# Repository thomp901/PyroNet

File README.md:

# PyroNet
Early Fire Detection: Purdue Senior Design Project

Team Members:
Sebastian Carrizosa
Kameron Jackson
Diego Ramirez
Garrison Thompson

## Download Specific Folders

To download **only** the a specific folder (e.g. hardware/, csp/) that contains the relevant files, run the following commands:

```bash
git clone --filter=blob:none --no-checkout https://github.com/thomp901/PyroNet.git
cd PyroNet
git sparse-checkout init --cone
git sparse-checkout set FOLDER/
git checkout main
```

Replace `FOLDER` with the specfic folder.

Then, you can `pull`, `add`, `commit`, and `push` like normal.

## Pushing

To push, go to the project directory in your terminal and enter the following commands:

```bash
git add .
git commit -m 'YOUR MESSAGE'
git push
```

Replace `YOUR MESSAGE` with a brief description of your changes.

## Discarding your changes

To **discard your changes** and pull the latest version, enter: 

```bash
git fetch --all
git reset --hard origin/main
```

> [!WARNING]
> Warning: This will permanently delete any local work.

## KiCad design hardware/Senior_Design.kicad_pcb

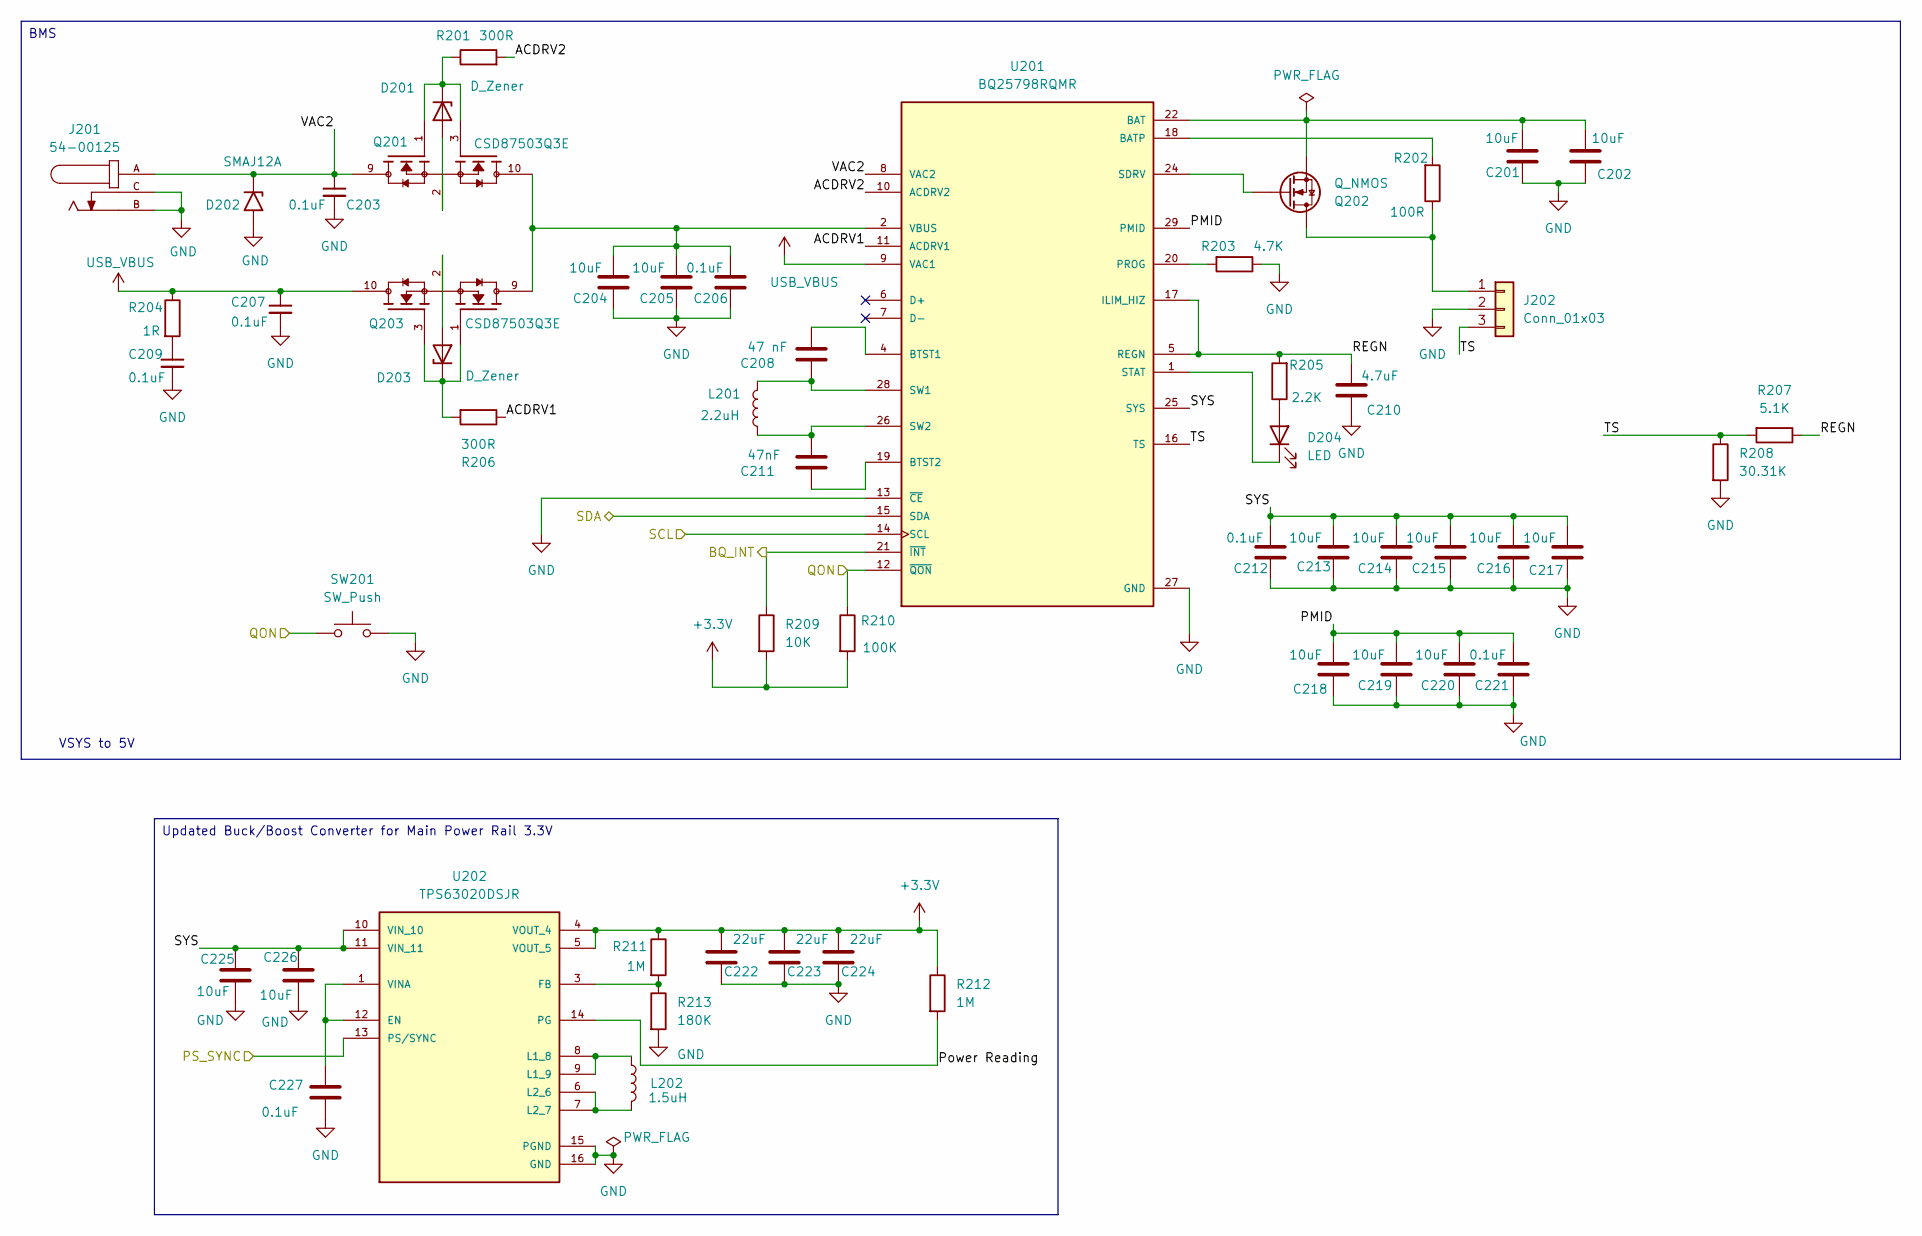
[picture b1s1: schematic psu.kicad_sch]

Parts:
C201, C202, C225, C226: 10uF; C_0603_1608Metric
C203, C207, C209: 0.1uF; C_0805_2012Metric
C204, C205, C213, C214, C215, C216, C217, C218, C219, C220: 10uF; C_0805_2012Metric
C206, C212, C221: 0.1uF; C_0402_1005Metric
C208: 47 nF; C_0603_1608Metric
C210: 4.7uF; C_0603_1608Metric
C211: 47nF; C_0603_1608Metric
C222, C223, C224: 22uF; C_0603_1608Metric
C227: 0.1uF; C_0603_1608Metric
D201, D203: D_Zener; D_SOD-123
D202: SMAJ12A; D_SMA
D204: LED; LED_0805_2012Metric
J201: 54-00125; TENSILITY_54-00125; PARTREV A; DigiKey_Part_Number 839-54-00125-ND
J202: Conn_01x03; JST_PH_S3B-PH-K_1x03_P2.00mm_Horizontal
L201: 2.2uH; L_Bourns_SRP7028A_7.3x6.6mm
L202: 1.5uH; L_Wuerth_MAPI-4020
Q201, Q203: CSD87503Q3E; TRANS_CSD87503Q3ET; PARTREV SEPTEMBER 2017; DigiKey_Part_Number 296-47497-1-ND
Q202: Q_NMOS; SOT-23_Handsoldering
R201, R206: 300R; R_0805_2012Metric
R202: 100R; R_0805_2012Metric
R203: 4.7K; R_0805_2012Metric
R204: 1R; R_0805_2012Metric
R205: 2.2K; R_0805_2012Metric
R207: 5.1K; R_0805_2012Metric
R208: 30.31K; R_0805_2012Metric
R209: 10K; R_0805_2012Metric
R210: 100K; R_0805_2012Metric
R211: 1M; R_0603_1608Metric
R212: 1M; R_0805_2012Metric
R213: 180K; R_0603_1608Metric
SW201: SW_Push; SW_SPST_TL3305A
U201: BQ25798RQMR; IC_BQ25798RQMR; PARTREV B
U202: TPS63020DSJR; IC_TPS63020DSJR

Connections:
+3.3V: C222.2, C223.2, C224.2, R209.2, R210.2, R211.1, R212.1, U202.4 (VOUT_4), U202.5 (VOUT_5); also elsewhere on the board
/BME 688 and SPS30/SCL: U201.14 (SCL); also elsewhere on the board
/BME 688 and SPS30/SDA: U201.15 (SDA); also elsewhere on the board
/BMS/ACDRV1: R206.1, U201.11 (ACDRV1)
/BMS/ACDRV2: R201.2, U201.10 (ACDRV2)
/BMS/BQ_INT: R209.1, U201.21 (~INT); also elsewhere on the board
/BMS/PMID: C218.1, C219.1, C220.1, C221.1, U201.29 (PMID)
/BMS/PS_SYNC: U202.13 (PS/SYNC); also elsewhere on the board
/BMS/Power Reading: R212.2, U202.14 (PG)
/BMS/QON: R210.1, SW201.1, U201.12 (~QON); also elsewhere on the board
/BMS/REGN: C210.1, R205.2, R207.1, U201.5 (REGN), U201.17 (ILIM_HIZ)
/BMS/SYS: C212.1, C213.1, C214.1, C215.1, C216.1, C217.1, C225.1, C226.1, U201.25 (SYS), U202.10 (VIN_10), U202.11 (VIN_11)
/BMS/TS: J202.3, R207.2, R208.1, U201.16 (TS)
/BMS/VAC2: C203.1, D202.1 (A1), J201.A, Q201.9, Q201.9.1, Q201.9.2, U201.8 (VAC2)
BAT: C201.1, C202.1, Q202.2 (S), U201.22 (BAT), U201.23 (BAT)
GND: C201.2, C202.2, C203.2, C204.2, C205.2, C206.2, C207.2, C209.2, C210.2, C212.2, C213.2, C214.2, C215.2, C216.2, C217.2, C218.2, C219.2, C220.2, C221.2, C222.1, C223.1, C224.1, C225.2, C226.2, C227.2, D202.2 (A2), J201.B, J201.C, J202.2, R203.1, R208.2, R213.2, SW201.2, U201.13 (~CE), U201.27 (GND), U202.2 (GND), U202.15 (PGND), U202.16 (GND), U202.17 (GND), U202.18 (GND), U202.19 (GND), U202.20 (GND), U202.21 (GND), U202.22 (GND), U202.23 (GND), U202.24 (GND), U202.25 (GND), U202.26 (GND), U202.27 (GND), U202.28 (GND), U202.29 (GND), U202.30 (GND); also elsewhere on the board
unnamed: C204.1, C205.1, C206.1, Q201.10, Q201.10.1, Q201.10.2, Q203.9, Q203.9.1, Q203.9.2, U201.2 (VBUS), U201.3 (VBUS)
unnamed: C209.1, R204.2
unnamed: D201.2 (A), Q201.2, Q201.4
unnamed: D201.1 (K), Q201.1, Q201.3, R201.1
unnamed: D203.2 (A), Q203.2, Q203.4
unnamed: D203.1 (K), Q203.1, Q203.3, R206.2
unnamed: D204.2 (A), R205.1
unnamed: D204.1 (K), U201.1 (STAT)
unnamed: J202.1, Q202.1 (D), R202.1
unnamed: Q202.3 (G), U201.24 (SDRV)
unnamed: R202.2, U201.18 (BATP)
unnamed: C208.1, U201.4 (BTST1)
unnamed: C211.2, U201.19 (BTST2)
unnamed: R203.2, U201.20 (PROG)
unnamed: C208.2, L201.2, U201.28 (SW1)
unnamed: C211.1, L201.1, U201.26 (SW2)
unnamed: C227.1, U202.1 (VINA), U202.12 (EN)
unnamed: R211.2, R213.1, U202.3 (FB)
unnamed: L202.1, U202.8 (L1_8), U202.9 (L1_9)
unnamed: L202.2, U202.6 (L2_6), U202.7 (L2_7)
USB_VBUS: C207.1, Q203.10, Q203.10.1, Q203.10.2, R204.1, U201.9 (VAC1); also elsewhere on the board

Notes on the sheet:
VSYS to 5V
Updated Buck/Boost Converter for Main Power Rail 3.3V
BMS

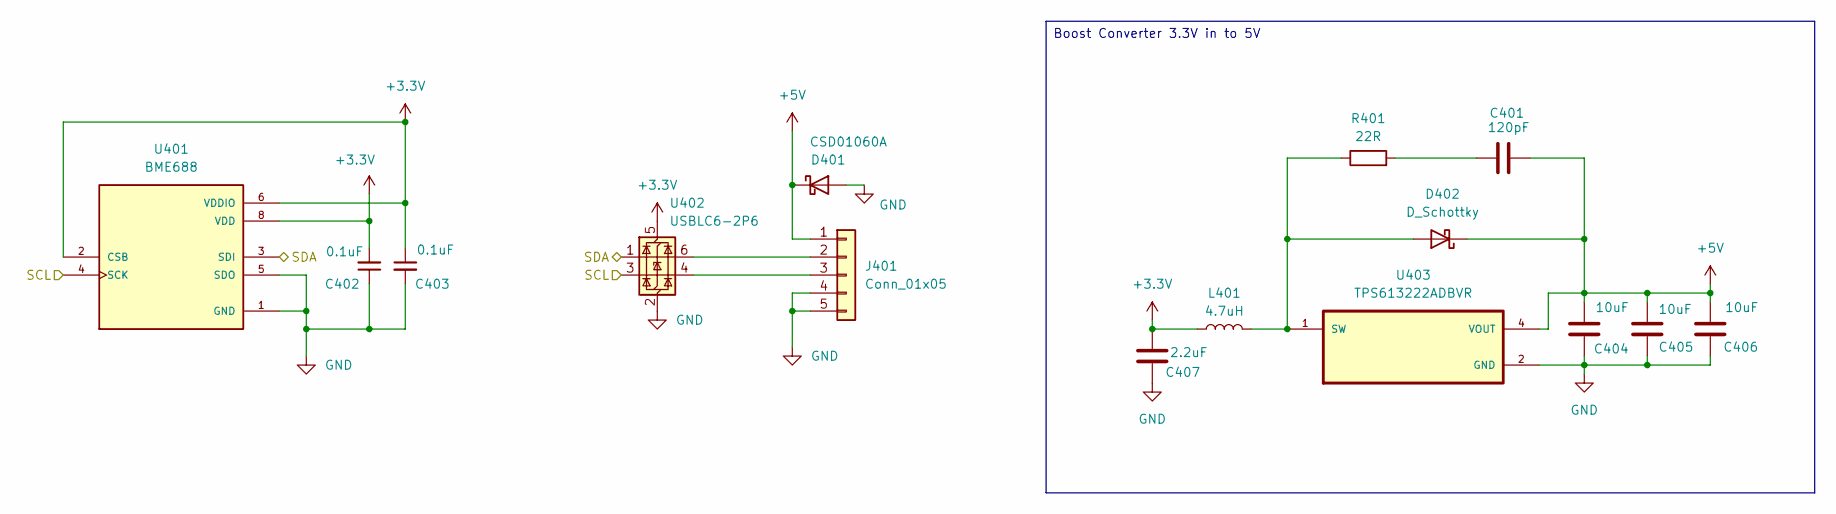
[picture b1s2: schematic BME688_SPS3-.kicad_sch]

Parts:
C401: 120pF; C_0402_1005Metric
C402, C403: 0.1uF; C_0805_2012Metric
C404, C405, C406: 10uF; C_0603_1608Metric
C407: 2.2uF; C_0603_1608Metric
D401: CSD01060A; D_SOD-123
D402: D_Schottky; D_0805_2012Metric
J401: Conn_01x05; JST_ZH_B5B-ZR_1x05_P1.50mm_Vertical
L401: 4.7uH; L_1008_2520Metric
R401: 22R; R_0402_1005Metric
U401: BME688; IC_BME688; PARTREV 1.0
U402: USBLC6-2P6; SOT-666
U403: TPS613222ADBVR; SOT95P280X145-5N; DigiKey_Part_Number 296-50503-1-ND

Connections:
+3.3V: C402.2, C403.1, C407.2, L401.1, U401.2 (CSB), U401.6 (VDDIO), U401.8 (VDD), U402.5 (VBUS); also elsewhere on the board
+5V: C401.1, C404.2, C405.2, C406.2, D401.1 (K), D402.1 (K), J401.1, U403.4 (VOUT)
/BME 688 and SPS30/SCL: U401.4 (SCK), U402.3 (I/O2); also elsewhere on the board
/BME 688 and SPS30/SDA: U401.3 (SDI), U402.1 (I/O1); also elsewhere on the board
GND: C402.1, C403.2, C404.1, C405.1, C406.1, C407.1, D401.2 (A), J401.4, J401.5, U401.1 (GND), U401.5 (SDO), U401.7 (GND), U402.2 (GND), U403.2 (GND); also elsewhere on the board
unnamed: C401.2, R401.2
unnamed: D402.2 (A), L401.2, R401.1, U403.1 (SW)
unnamed: J401.2, U402.6 (I/O1)
unnamed: J401.3, U402.4 (I/O2)

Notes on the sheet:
Boost Converter 3.3V in to 5V

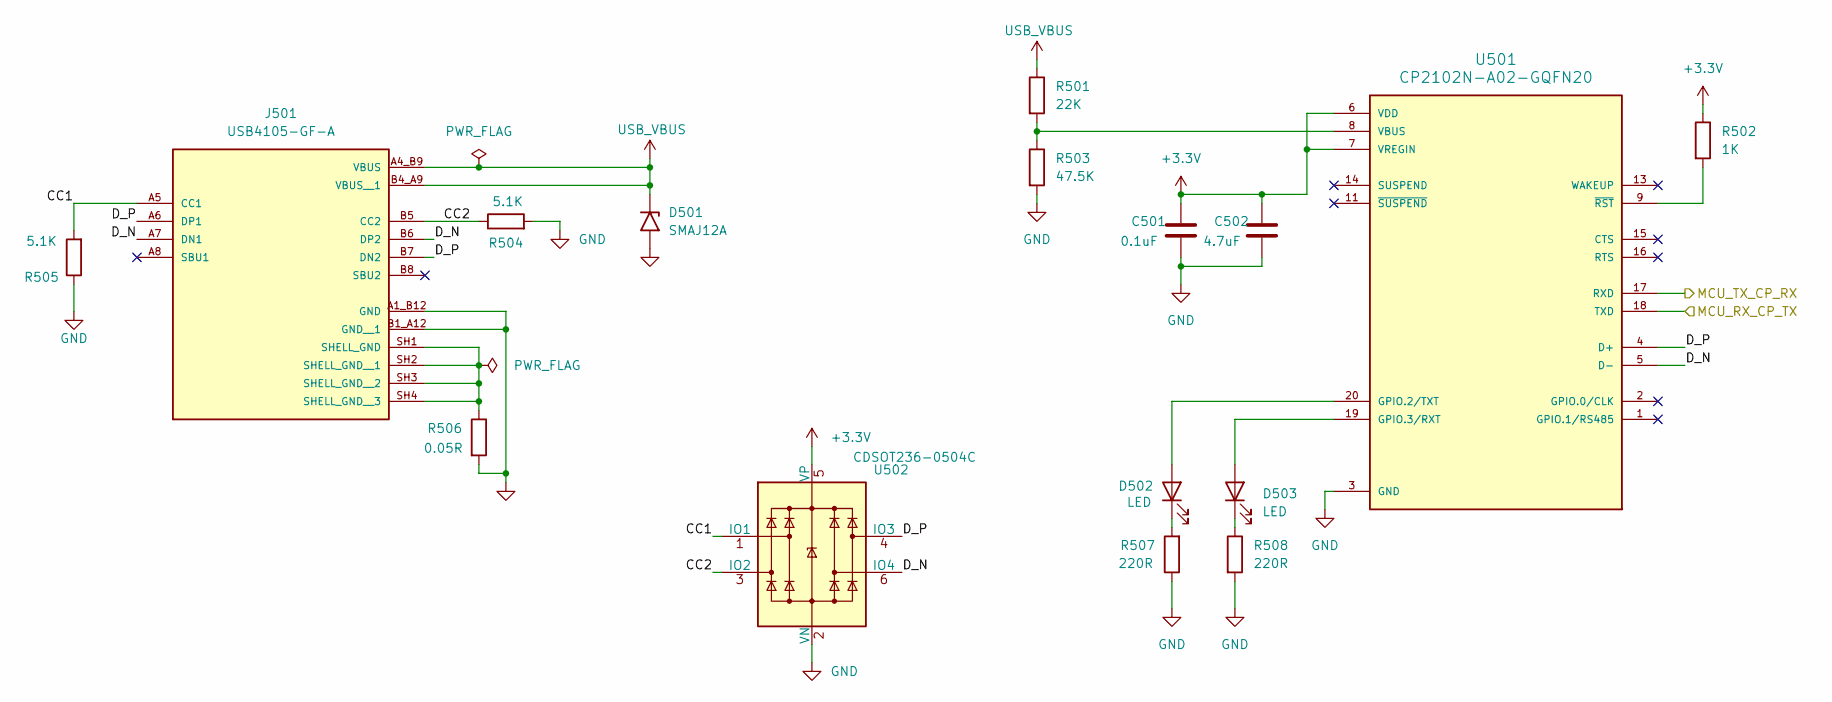
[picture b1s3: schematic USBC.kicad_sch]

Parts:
C501: 0.1uF; C_0603_1608Metric
C502: 4.7uF; C_0603_1608Metric
D501: SMAJ12A; D_SMA
D502, D503: LED; LED_0805_2012Metric
J501: USB4105-GF-A; GCT_USB4105-GF-A; PARTREV B4
R501: 22K; R_0805_2012Metric
R502: 1K; R_0805_2012Metric
R503: 47.5K; R_0805_2012Metric
R504, R505: 5.1K; R_0805_2012Metric
R506: 0.05R; R_0805_2012Metric
R507, R508: 220R; R_0805_2012Metric
U501: CP2102N-A02-GQFN20; SILABS_CP2102N-A02-GQFN20R; PARTREV 1.3
U502: CDSOT236-0504C; SOT-23-6

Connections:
+3.3V: C501.1, C502.1, R502.1, U501.6 (VDD), U501.7 (VREGIN), U502.5 (VP); also elsewhere on the board
/MCU/MCU_RX_CP_TX: U501.18 (TXD); also elsewhere on the board
/MCU/MCU_TX_CP_RX: U501.17 (RXD); also elsewhere on the board
/USB-C/CC1: J501.A5 (CC1), R505.2, U502.1 (IO1)
/USB-C/CC2: J501.B5 (CC2), R504.1, U502.3 (IO2)
/USB-C/D_N: J501.A7 (DN1), J501.B6 (DP2), U501.5 (D-), U502.6 (IO4)
/USB-C/D_P: J501.A6 (DP1), J501.B7 (DN2), U501.4 (D+), U502.4 (IO3)
GND: C501.2, C502.2, D501.2 (A2), J501.A1_B12 (GND), J501.B1_A12 (GND__1), R503.2, R504.2, R505.1, R506.2, R507.1, R508.2, U501.3 (GND), U501.12 (GND), U501.21 (GND), U502.2 (VN); also elsewhere on the board
unnamed: D502.2 (A), U501.20 (GPIO.2/TXT)
unnamed: D502.1 (K), R507.2
unnamed: D503.2 (A), U501.19 (GPIO.3/RXT)
unnamed: D503.1 (K), R508.1
unnamed: J501.SH1 (SHELL_GND), J501.SH2 (SHELL_GND__1), J501.SH3 (SHELL_GND__2), J501.SH4 (SHELL_GND__3), R506.1
unnamed: R501.2, R503.1, U501.8 (VBUS)
unnamed: R502.2, U501.9 (~RST)
USB_VBUS: D501.1 (A1), J501.A4_B9 (VBUS), J501.B4_A9 (VBUS__1), R501.1; also elsewhere on the board

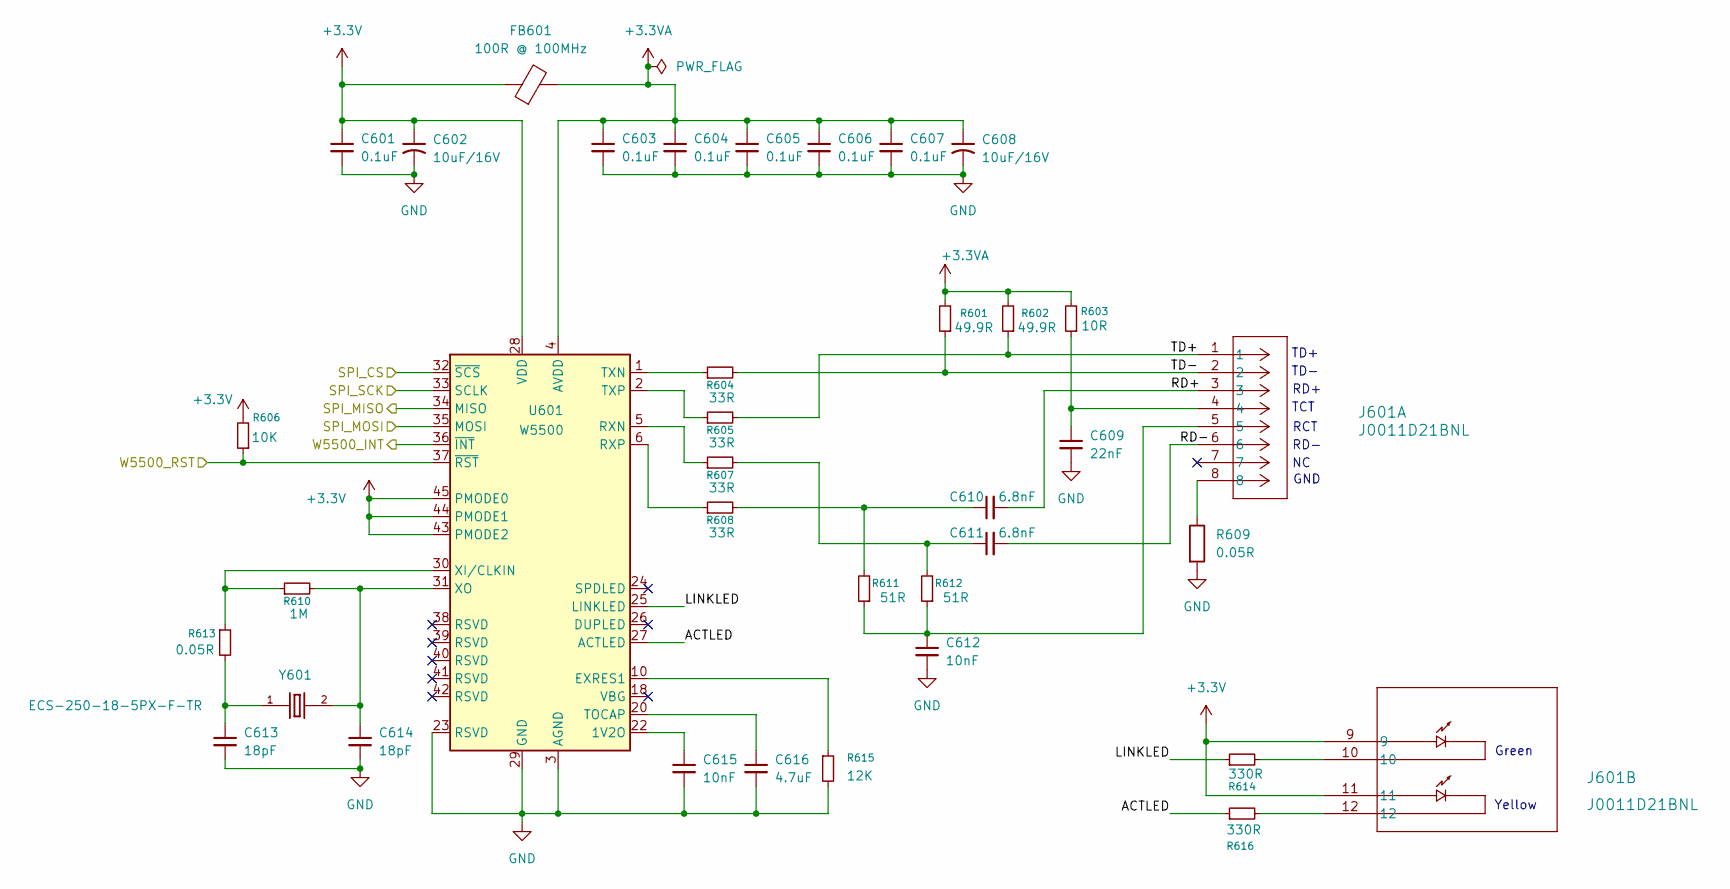
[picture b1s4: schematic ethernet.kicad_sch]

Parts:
C601, C603, C604, C605, C606, C607: 0.1uF; C_0603_1608Metric
C602, C608: 10uF/16V; C_0603_1608Metric
C609: 22nF; C_0805_2012Metric
C610, C611: 6.8nF; C_0805_2012Metric
C612, C615: 10nF; C_0805_2012Metric
C613, C614: 18pF; C_0805_2012Metric
C616: 4.7uF; C_0805_2012Metric
FB601: 100R @ 100MHz; R_0603_1608Metric
J601: J0011D21BNL; CONN_J0011D21B_PUL
R601, R602: 49.9R; R_0805_2012Metric
R603: 10R; R_0805_2012Metric
R604, R605, R607, R608: 33R; R_0805_2012Metric
R606: 10K; R_0603_1608Metric
R609, R613: 0.05R; R_0805_2012Metric
R610: 1M; R_0805_2012Metric
R611, R612: 51R; R_0805_2012Metric
R614, R616: 330R; R_0805_2012Metric
R615: 12K; R_0805_2012Metric
U601: W5500; LQFP-48_7x7mm_P0.5mm
Y601: ECS-250-18-5PX-F-TR; XTAL_ECS-250-18-5PX-F-TR; PARTREV 2017; DigiKey_Part_Number XC1305CT-ND

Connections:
+3.3V: C601.1, C602.1, FB601.1, J601.9, J601.11, R606.2, U601.28 (VDD), U601.43 (PMODE2), U601.44 (PMODE1), U601.45 (PMODE0); also elsewhere on the board
+3.3VA: C603.1, C604.1, C605.1, C606.1, C607.1, C608.1, FB601.2, R601.2, R602.2, R603.2, U601.4 (AVDD), U601.8 (AVDD), U601.11 (AVDD), U601.15 (AVDD), U601.17 (AVDD), U601.21 (AVDD)
/Ethernet/ACTLED: R616.1, U601.27 (ACTLED)
/Ethernet/LINKLED: R614.1, U601.25 (LINKLED)
/Ethernet/RD+: C610.2, J601.3
/Ethernet/RD-: C611.2, J601.6
/Ethernet/SPI_CS: U601.32 (~SCS); also elsewhere on the board
/Ethernet/SPI_MISO: U601.34 (MISO); also elsewhere on the board
/Ethernet/SPI_MOSI: U601.35 (MOSI); also elsewhere on the board
/Ethernet/SPI_SCK: U601.33 (SCLK); also elsewhere on the board
/Ethernet/TD+: J601.1, R602.1, R605.2
/Ethernet/TD-: J601.2, R601.1, R604.2
/Ethernet/W5500_INT: U601.36 (~INT); also elsewhere on the board
/Ethernet/W5500_RST: R606.1, U601.37 (~RST); also elsewhere on the board
GND: C601.2, C602.2, C603.2, C604.2, C605.2, C606.2, C607.2, C608.2, C609.2, C612.2, C613.2, C614.2, C615.2, C616.2, R609.2, R615.2, U601.3 (AGND), U601.9 (AGND), U601.14 (AGND), U601.16 (AGND), U601.19 (AGND), U601.23 (RSVD), U601.29 (GND), U601.48 (AGND); also elsewhere on the board
unnamed: C609.1, J601.4, R603.1
unnamed: C610.1, R608.2, R611.2
unnamed: C611.1, R607.2, R612.2
unnamed: C612.1, J601.5, R611.1, R612.1
unnamed: C613.1, R613.2, Y601.1
unnamed: J601.8, R609.1
unnamed: J601.10, R614.2
unnamed: J601.12, R616.2
unnamed: C615.1, U601.22 (1V2O)
unnamed: R615.1, U601.10 (EXRES1)
unnamed: R607.1, U601.5 (RXN)
unnamed: R608.1, U601.6 (RXP)
unnamed: C616.1, U601.20 (TOCAP)
unnamed: R604.1, U601.1 (TXN)
unnamed: R605.1, U601.2 (TXP)
unnamed: R610.1, R613.1, U601.30 (XI/CLKIN)
unnamed: C614.1, R610.2, U601.31 (XO), Y601.2

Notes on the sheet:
TD+
GND
TD-
TCT
Green
RCT
Yellow
RD+
RD-

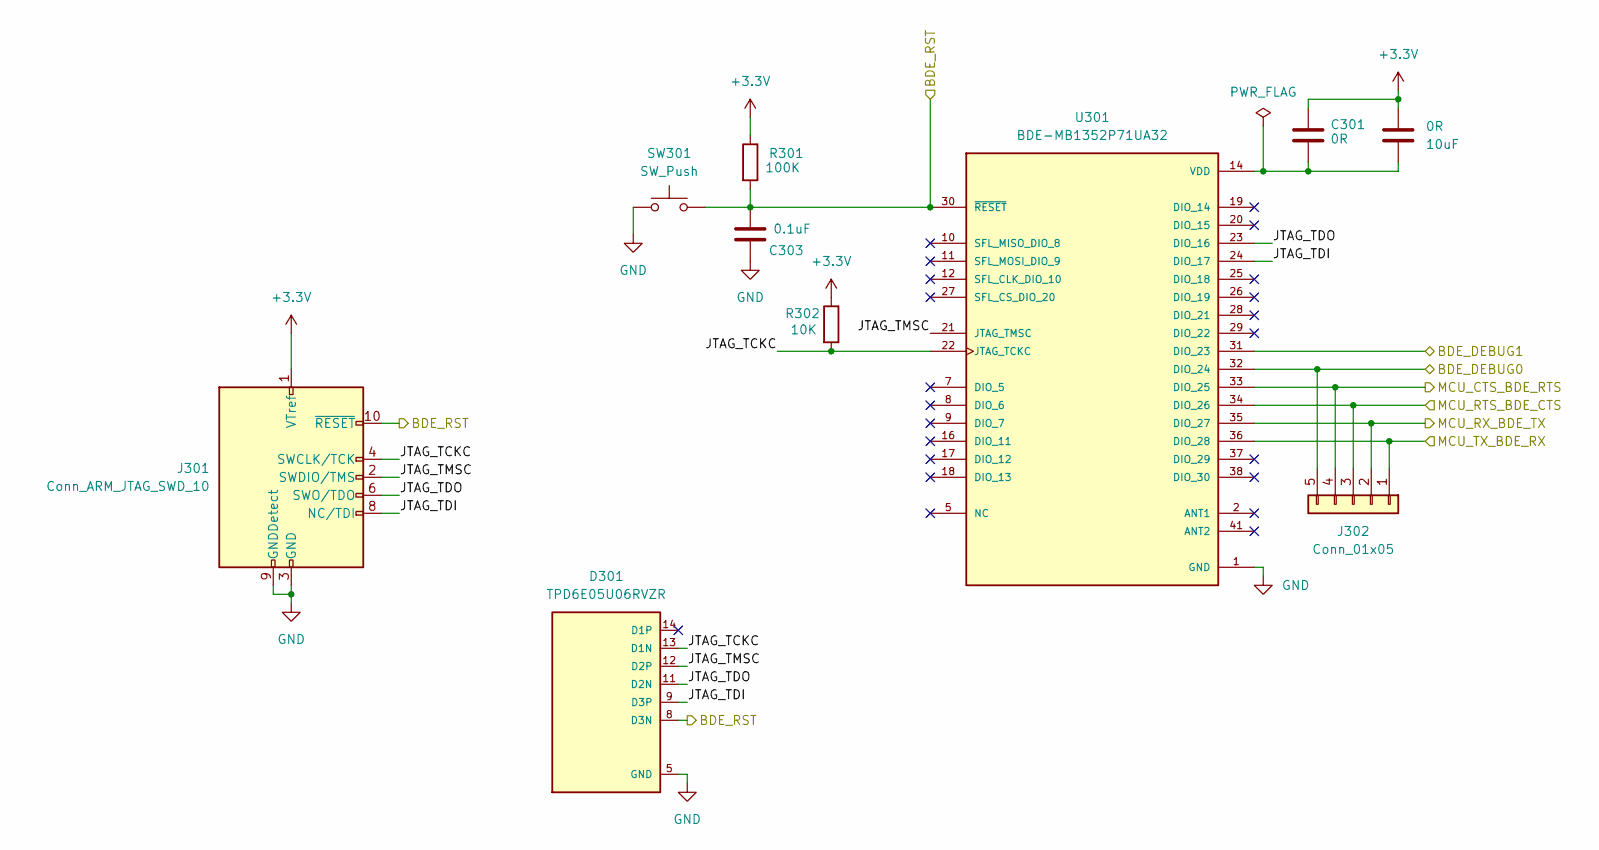
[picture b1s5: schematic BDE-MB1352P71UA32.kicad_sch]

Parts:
0R: 10uF; C_0805_2012Metric
C301: 0R; C_0805_2012Metric
C303: 0.1uF; C_0805_2012Metric
D301: TPD6E05U06RVZR; SON50P135X350X55-14N; PARTREV L; DigiKey_Part_Number 296-39349-1-ND
J301: Conn_ARM_JTAG_SWD_10; PinHeader_2x05_P1.27mm_Vertical_SMD
J302: Conn_01x05; PinHeader_1x05_P2.54mm_Vertical
R301: 100K; R_0805_2012Metric
R302: 10K; R_0805_2012Metric
SW301: SW_Push; SW_SPST_TL3305A
U301: BDE-MB1352P71UA32; XCVR_BDE-MB1352P71UA32_1.03; PARTREV V1.1

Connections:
+3.3V: 0R.1, C301.1, J301.1 (VTref), R301.1, R302.1; also elsewhere on the board
/MCU/BDE_DEBUG0: J302.5, U301.32 (DIO_24); also elsewhere on the board
/MCU/BDE_DEBUG1: U301.31 (DIO_23); also elsewhere on the board
/MCU/BDE_RST: C303.1, D301.8 (D3N), J301.10 (~RESET), R301.2, SW301.2, U301.30 (~RESET); also elsewhere on the board
/MCU/MCU_CTS_BDE_RTS: J302.4, U301.33 (DIO_25); also elsewhere on the board
/MCU/MCU_RTS_BDE_CTS: J302.3, U301.34 (DIO_26); also elsewhere on the board
/MCU/MCU_RX_BDE_TX: J302.1, U301.36 (DIO_28); also elsewhere on the board
/MCU/MCU_TX_BDE_RX: J302.2, U301.35 (DIO_27); also elsewhere on the board
/Wi-SUN Module/JTAG_TCKC: D301.13 (D1N), J301.4 (SWCLK/TCK), R302.2, U301.22 (JTAG_TCKC)
/Wi-SUN Module/JTAG_TDI: D301.9 (D3P), J301.8 (NC/TDI), U301.24 (DIO_17)
/Wi-SUN Module/JTAG_TDO: D301.11 (D2N), J301.6 (SWO/TDO), U301.23 (DIO_16)
/Wi-SUN Module/JTAG_TMSC: D301.12 (D2P), J301.2 (SWDIO/TMS), U301.21 (JTAG_TMSC)
GND: C303.2, D301.5 (GND), D301.10 (GND), J301.3 (GND), J301.5 (GND), J301.9 (GNDDetect), SW301.1, U301.1 (GND), U301.3 (GND), U301.4 (GND), U301.13 (GND), U301.39 (GND), U301.40 (GND), U301.42 (GND); also elsewhere on the board
VDD: 0R.2, C301.2, U301.14 (VDD), U301.15 (VDD); also elsewhere on the board

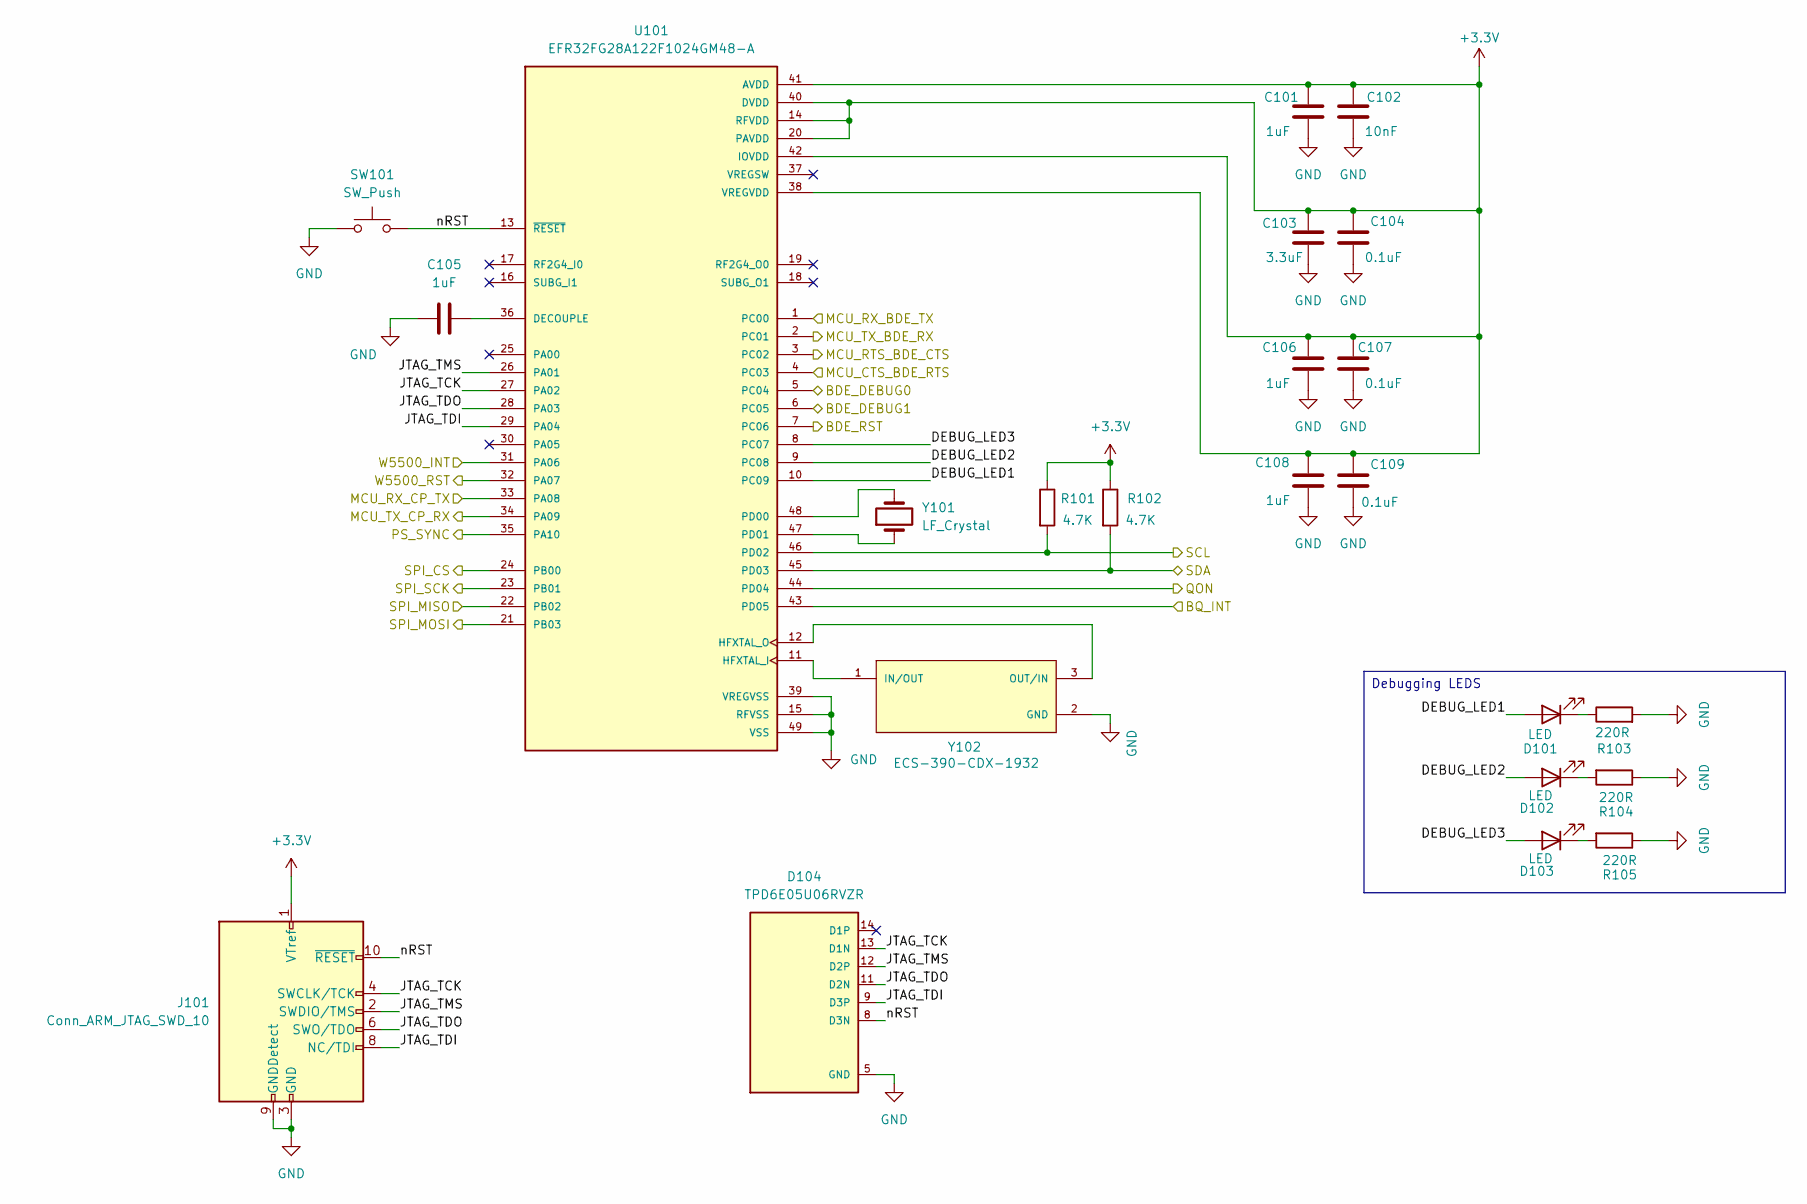
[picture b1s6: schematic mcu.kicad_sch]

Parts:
C101, C106, C108: 1uF; C_0603_1608Metric
C102: 10nF; C_0603_1608Metric
C103: 3.3uF; C_0603_1608Metric
C104, C107, C109: 0.1uF; C_0603_1608Metric
C105: 1uF; C_0805_2012Metric
D101, D102, D103: LED; LED_0805_2012Metric
D104: TPD6E05U06RVZR; SON50P135X350X55-14N; PARTREV L; DigiKey_Part_Number 296-39349-1-ND
J101: Conn_ARM_JTAG_SWD_10; PinHeader_2x05_P1.27mm_Vertical_SMD
R101, R102: 4.7K; R_0805_2012Metric
R103, R104, R105: 220R; R_0805_2012Metric
SW101: SW_Push; SW_SPST_TL3305A
U101: EFR32FG28A122F1024GM48-A; QFN40P600X600X90-49N; PARTREV 1.1
Y101: LF_Crystal; Crystal_SMD_3215-2Pin_3.2x1.5mm
Y102: ECS-390-CDX-1932; XTAL_ECS-390-CDX-1932

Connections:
+3.3V: C101.1, C102.1, C103.1, C104.1, C106.1, C107.1, C108.1, C109.1, J101.1 (VTref), R101.1, R102.1, U101.14 (RFVDD), U101.20 (PAVDD), U101.38 (VREGVDD), U101.40 (DVDD), U101.41 (AVDD), U101.42 (IOVDD); also elsewhere on the board
/BME 688 and SPS30/SCL: R101.2, U101.46 (PD02); also elsewhere on the board
/BME 688 and SPS30/SDA: R102.2, U101.45 (PD03); also elsewhere on the board
/BMS/BQ_INT: U101.43 (PD05); also elsewhere on the board
/BMS/PS_SYNC: U101.35 (PA10); also elsewhere on the board
/BMS/QON: U101.44 (PD04); also elsewhere on the board
/Ethernet/SPI_CS: U101.24 (PB00); also elsewhere on the board
/Ethernet/SPI_MISO: U101.22 (PB02); also elsewhere on the board
/Ethernet/SPI_MOSI: U101.21 (PB03); also elsewhere on the board
/Ethernet/SPI_SCK: U101.23 (PB01); also elsewhere on the board
/Ethernet/W5500_INT: U101.31 (PA06); also elsewhere on the board
/Ethernet/W5500_RST: U101.32 (PA07); also elsewhere on the board
/MCU/BDE_DEBUG0: U101.5 (PC04); also elsewhere on the board
/MCU/BDE_DEBUG1: U101.6 (PC05); also elsewhere on the board
/MCU/BDE_RST: U101.7 (PC06); also elsewhere on the board
/MCU/DEBUG_LED1: D101.2 (A), U101.10 (PC09)
/MCU/DEBUG_LED2: D102.2 (A), U101.9 (PC08)
/MCU/DEBUG_LED3: D103.2 (A), U101.8 (PC07)
/MCU/JTAG_TCK: D104.13 (D1N), J101.4 (SWCLK/TCK), U101.27 (PA02)
/MCU/JTAG_TDI: D104.9 (D3P), J101.8 (NC/TDI), U101.29 (PA04)
/MCU/JTAG_TDO: D104.11 (D2N), J101.6 (SWO/TDO), U101.28 (PA03)
/MCU/JTAG_TMS: D104.12 (D2P), J101.2 (SWDIO/TMS), U101.26 (PA01)
/MCU/MCU_CTS_BDE_RTS: U101.4 (PC03); also elsewhere on the board
/MCU/MCU_RTS_BDE_CTS: U101.3 (PC02); also elsewhere on the board
/MCU/MCU_RX_BDE_TX: U101.1 (PC00); also elsewhere on the board
/MCU/MCU_RX_CP_TX: U101.33 (PA08); also elsewhere on the board
/MCU/MCU_TX_BDE_RX: U101.2 (PC01); also elsewhere on the board
/MCU/MCU_TX_CP_RX: U101.34 (PA09); also elsewhere on the board
/MCU/nRST: D104.8 (D3N), J101.10 (~RESET), SW101.2, U101.13 (~RESET)
GND: C101.2, C102.2, C103.2, C104.2, C105.1, C106.2, C107.2, C108.2, C109.2, D104.5 (GND), D104.10 (GND), J101.3 (GND), J101.5 (GND), J101.9 (GNDDetect), R103.2, R104.1, R105.1, SW101.1, U101.15 (RFVSS), U101.39 (VREGVSS), U101.49 (VSS), Y102.2 (GND), Y102.4 (GND__1); also elsewhere on the board
unnamed: D101.1 (K), R103.1
unnamed: D102.1 (K), R104.2
unnamed: D103.1 (K), R105.2
unnamed: C105.2, U101.36 (DECOUPLE)
unnamed: U101.11 (HFXTAL_I), Y102.1 (IN/OUT)
unnamed: U101.12 (HFXTAL_O), Y102.3 (OUT/IN)
unnamed: U101.48 (PD00), Y101.2
unnamed: U101.47 (PD01), Y101.1

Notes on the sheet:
Debugging LEDS

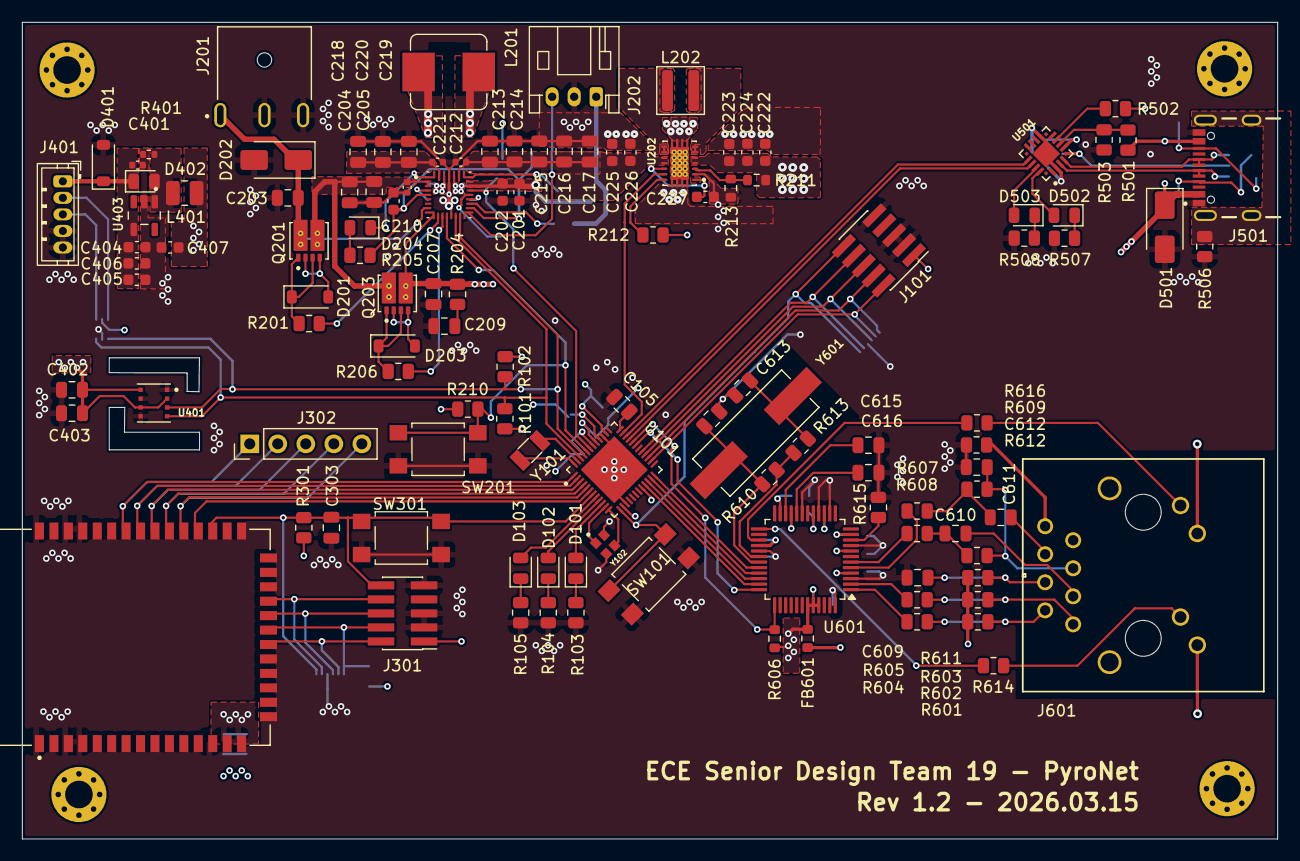
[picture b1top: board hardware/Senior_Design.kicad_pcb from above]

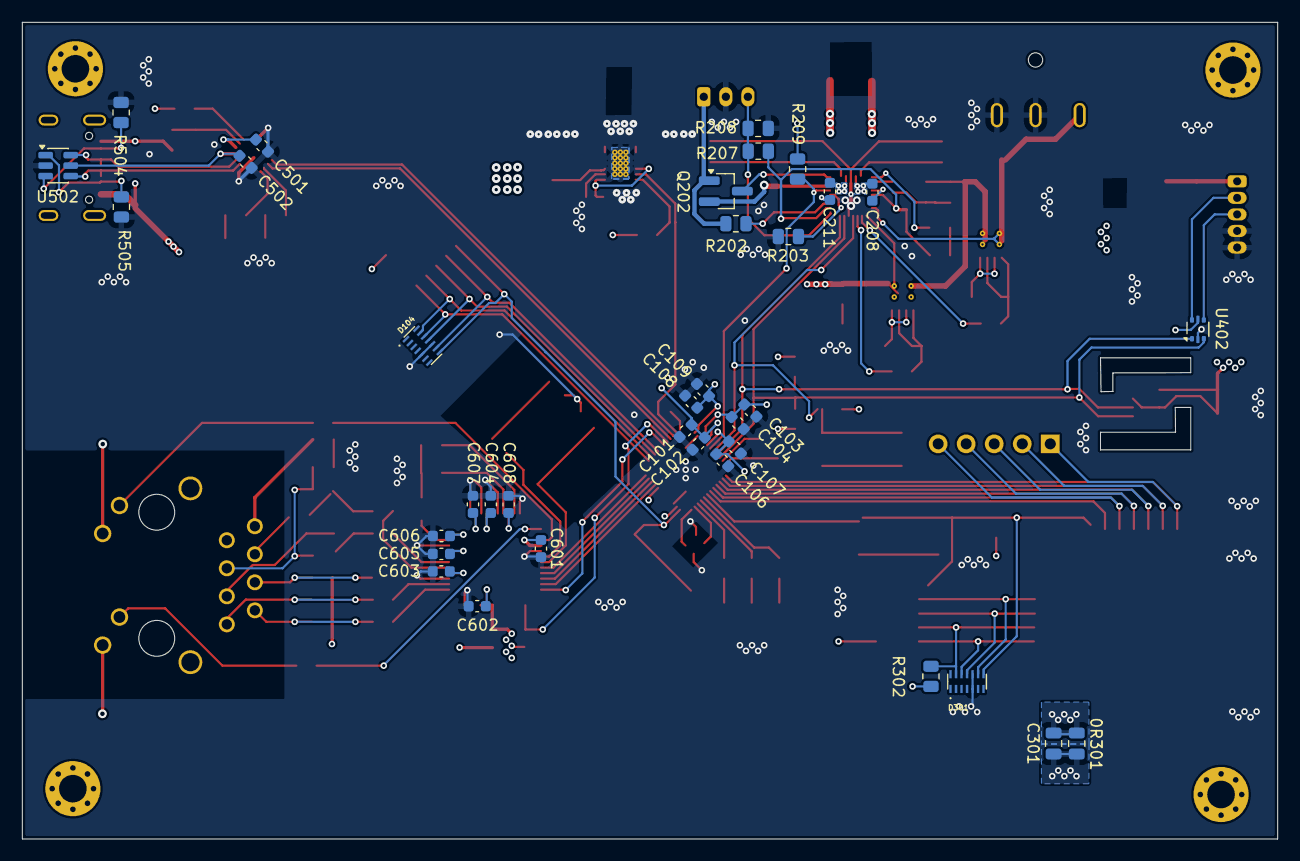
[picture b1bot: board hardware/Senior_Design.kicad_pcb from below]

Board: 4 copper layers, 113.8 x 74.0 mm, 154 parts (35 on the bottom side), 113 nets.

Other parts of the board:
0R301: 10uF; C_0805_2012Metric

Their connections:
+3.3V: 0R301.1; also elsewhere on the board
VDD: 0R301.2; also elsewhere on the board
